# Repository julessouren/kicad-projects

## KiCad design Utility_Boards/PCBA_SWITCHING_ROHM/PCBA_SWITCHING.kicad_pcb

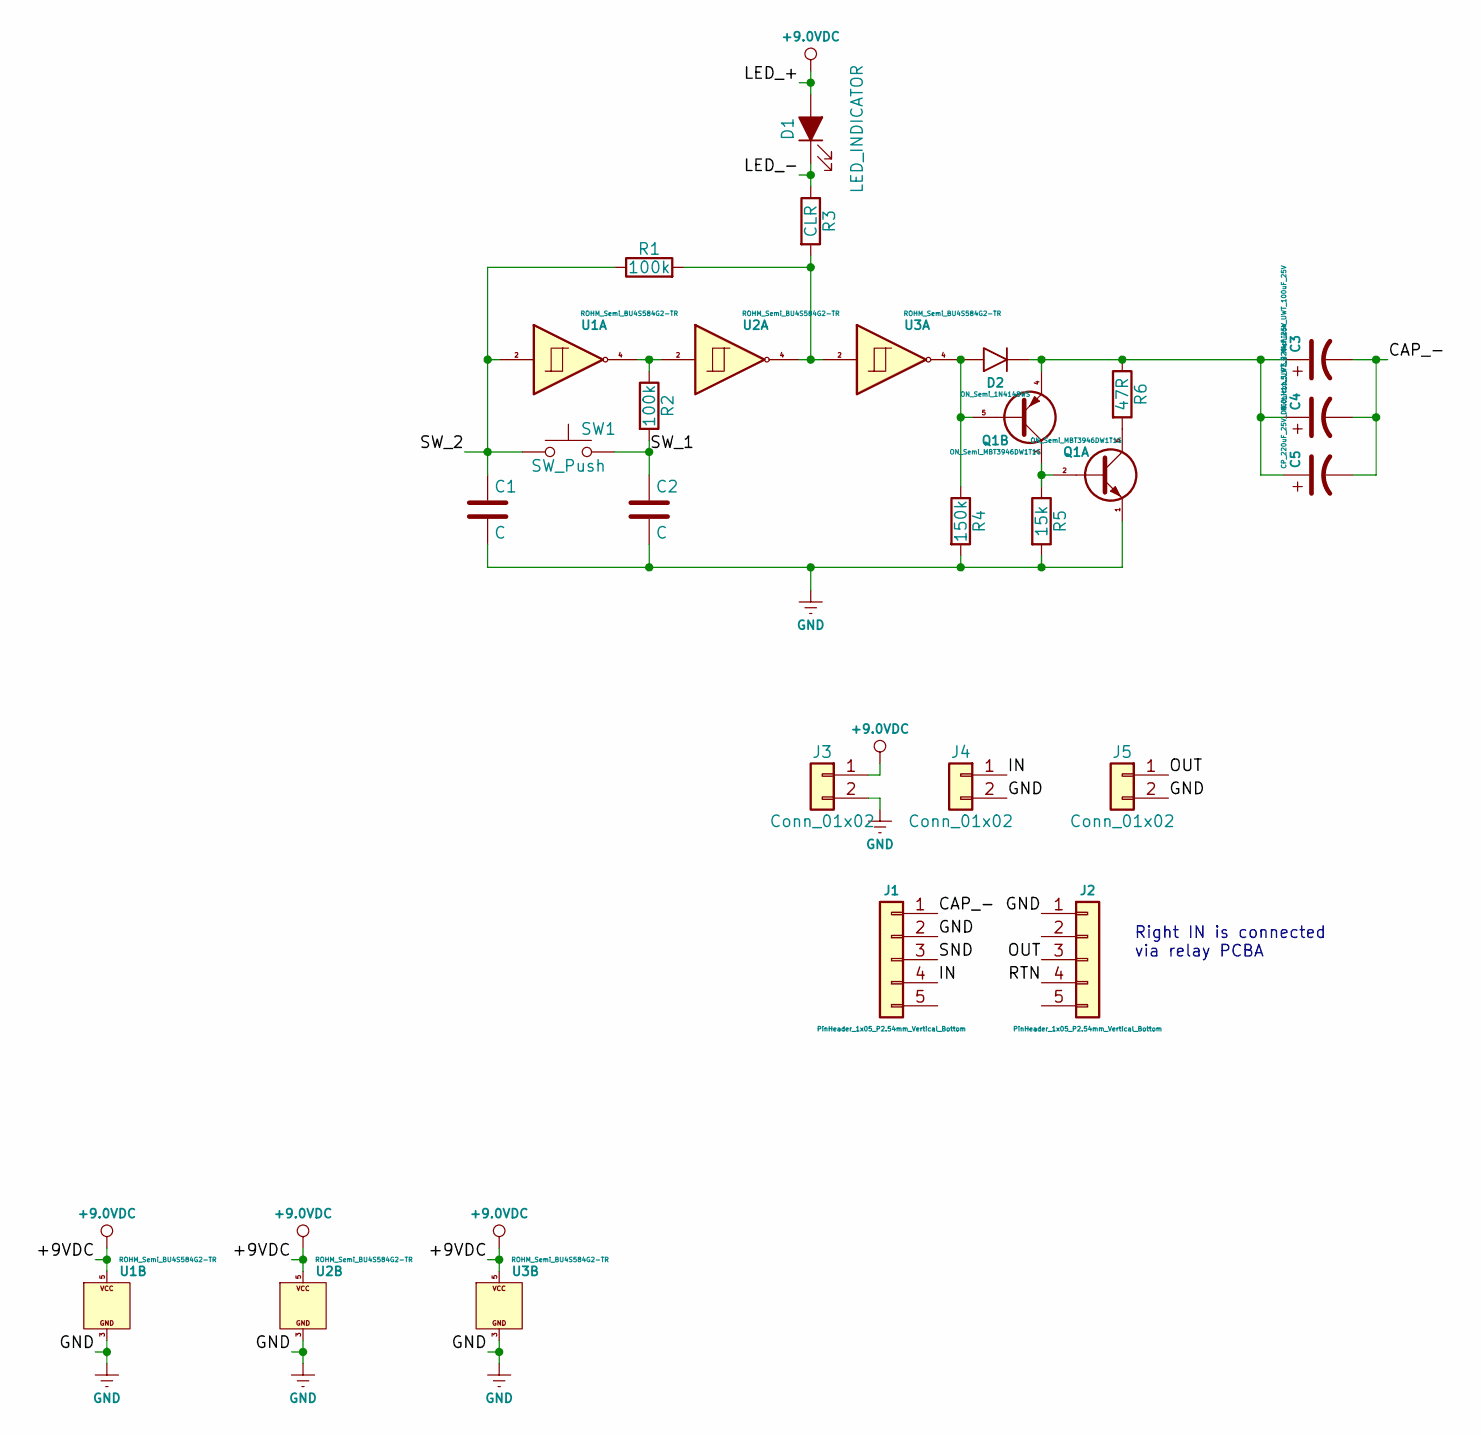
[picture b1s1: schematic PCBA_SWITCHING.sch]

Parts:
C1, C2: C; C_0603_1608M
C3: Nichicon_UWT_100uF_25V; Nichicon_UWT1E101MCL1GS_100uF_25V_6.3x7.7mm
C4: Nichicon_UWT_220uF_25V; Nichicon_UWT1E221MNL1GS_220uF_25V_8.0x10.0mm
C5: CP_220uF_25V_D8.0_H11.5_P3.5; Capacitor_Electrolytic_Radial_D8.0_H11.5_P3.5
D1: LED_INDICATOR; Wire_Pad_2x_1.0mm_Hole_1.5_Annular
D2: ON_Semi_1N4148WS; ON_Semi_1N4148WS_SOD-323F-2
J1, J2: PinHeader_1x05_P2.54mm_Vertical_Bottom; PinHeader_1x05_P2.54mm_Vertical
J3, J4, J5: Conn_01x02; Wire_Pad_2x_1.0mm_Hole_1.5_Annular_2.54mm_Pitch
Q1: ON_Semi_MBT3946DW1T1G; ON_Semi_MBT3946DW1T1G_SOT-363_SC-70-6_SC-80
R1, R2: 100k; R_0603_1608M
R3: CLR; R_0603_1608M
R4: 150k; R_0603_1608M
R5: 15k; R_0603_1608M
R6: 47R; R_0603_1608M
SW1: SW_Push; Wire_Pad_2x_1.0mm_Hole_1.5_Annular_2.54mm_Pitch
U1, U2, U3: ROHM_Semi_BU4S584G2-TR; ROHM_Semi_BU4S584G2-TR_SSOP-5

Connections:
+9.0VDC: D1.2 (A), J3.1, U1.5, U2.5, U3.5
/CAP_-: C3.2, C4.2, C5.2, J1.1
/IN: J1.4, J4.1
/LED_-: D1.1 (K), R3.1
/OUT: J2.3, J5.1
/RTN: J2.4
/SND: J1.3
/SW_1: C2.1, R2.2, SW1.2
/SW_2: C1.1, R1.1, SW1.1, U1.2
GND: C1.2, C2.2, J1.2, J2.1, J3.2, J4.2, J5.2, Q1.1 (E1), R4.2, R5.2, U1.3, U2.3, U3.3
unnamed: C3.1, C4.1, C5.1, D2.1 (K), Q1.4 (E2), R6.1
unnamed: D2.2 (A), Q1.5 (B2), R4.1, U3.4
unnamed: Q1.2 (B1), Q1.3 (C2), R5.1
unnamed: Q1.6 (C1), R6.2
unnamed: R1.2, R3.2, U2.4, U3.2
unnamed: R2.1, U1.4, U2.2

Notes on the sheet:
Right IN is connected via relay PCBA

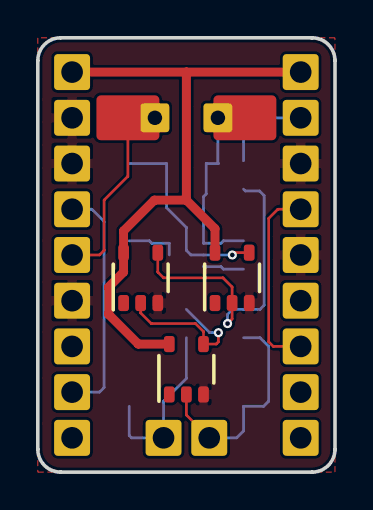
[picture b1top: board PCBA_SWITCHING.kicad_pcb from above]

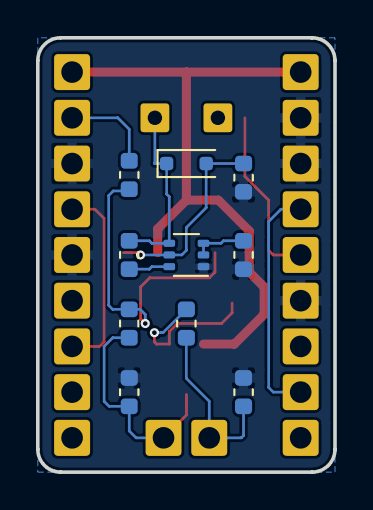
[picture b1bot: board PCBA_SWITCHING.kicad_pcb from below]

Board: 2 copper layers, 16.5 x 24.1 mm, 23 parts (10 on the bottom side), 14 nets.

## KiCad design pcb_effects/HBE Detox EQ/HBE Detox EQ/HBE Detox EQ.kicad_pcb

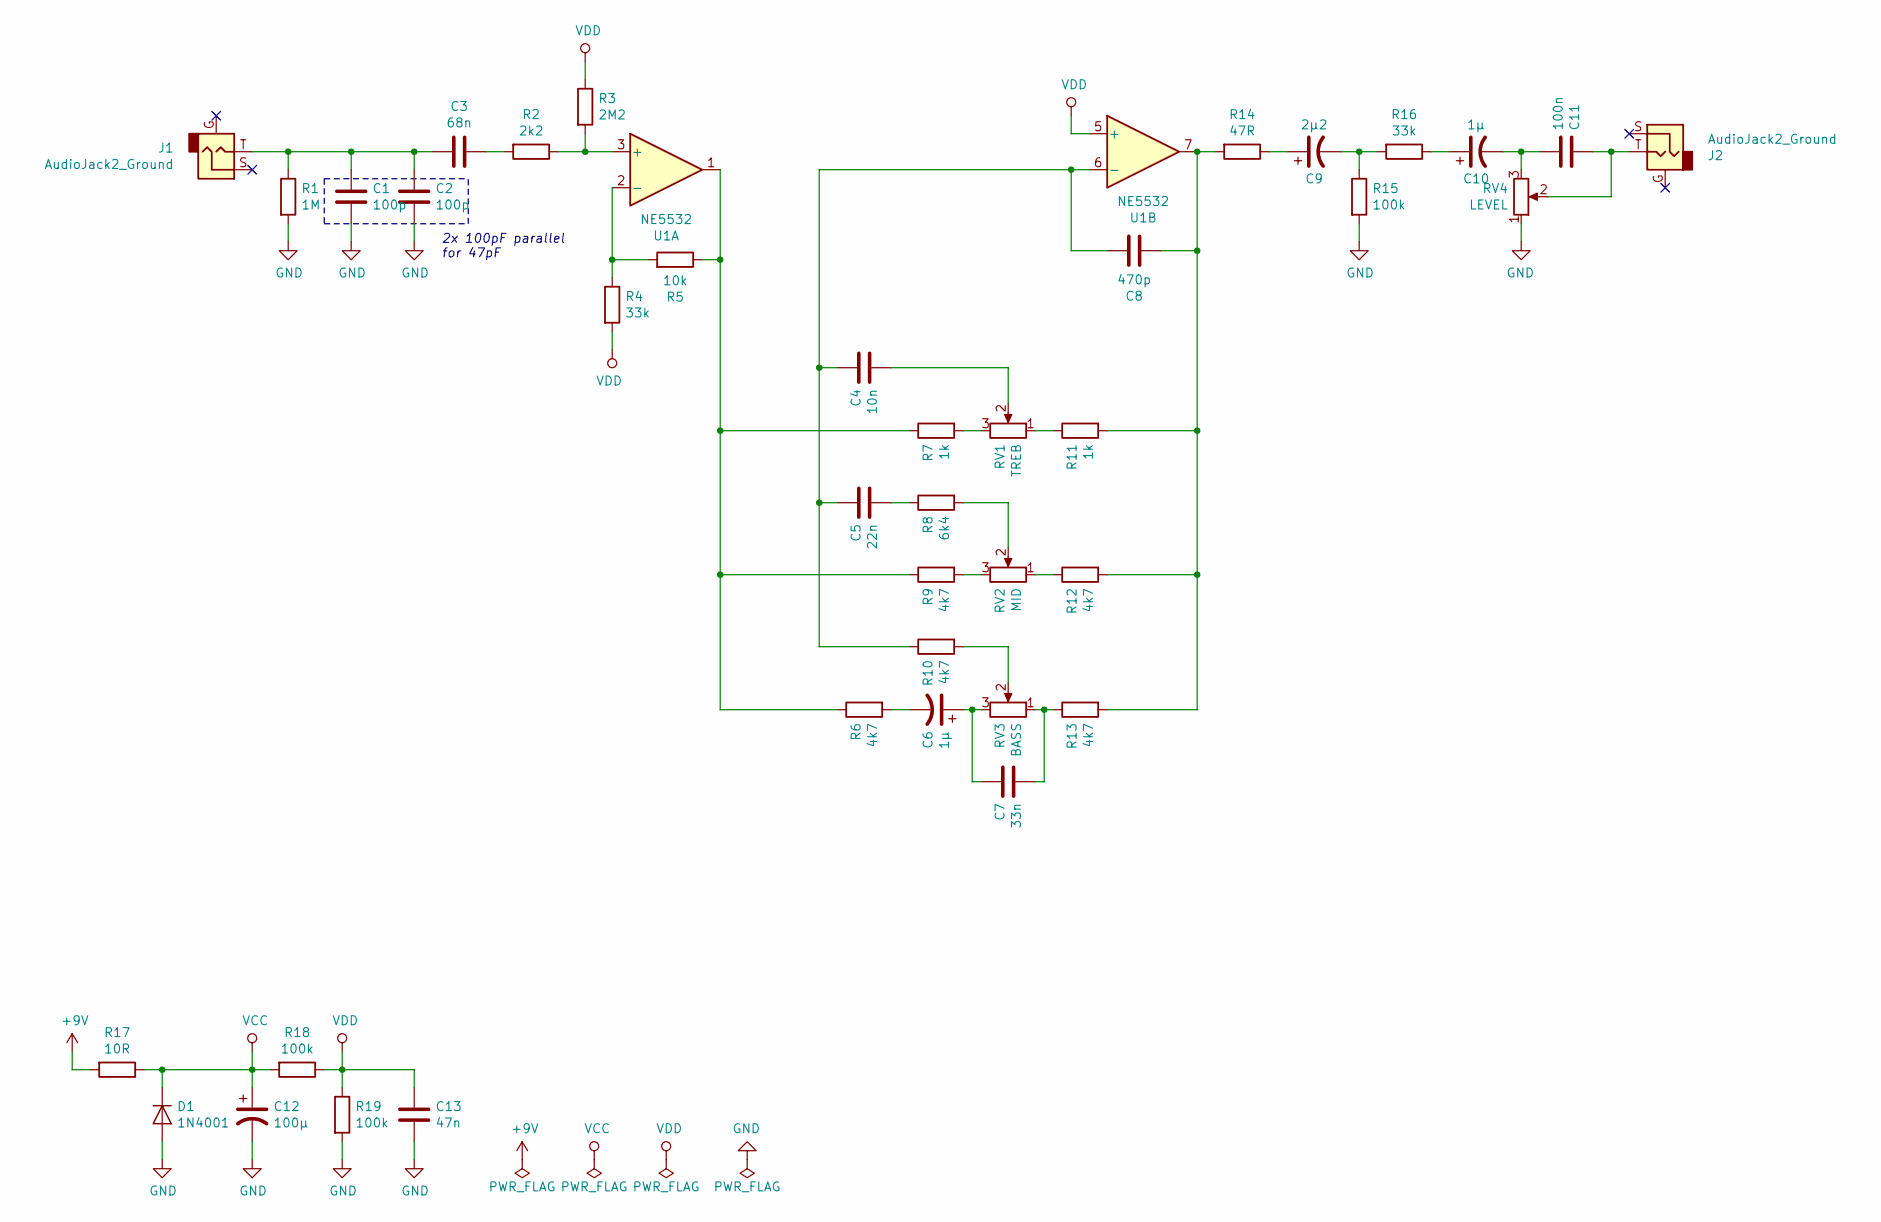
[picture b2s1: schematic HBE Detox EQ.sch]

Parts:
C1, C2: 100p; WIMA_FKP2J001001D00JSSD_100pF_P5.00_7.2x4.5x6.0mm
C3: 68n; WIMA_MKS2F026801C00KSSD_68nF_P5.00_7.2x3.5x8.5mm
C4: 10n; WIMA_FKS2G021001C00KSSD_10nF_P5.00_7.2x3.5x8.5mm
C5: 22n; WIMA_MKS2F022201A00KSSD_22nF_P5.00_7.2x2.5x6.5mm
C6, C10: 1µ; WIMA_MKS2C041001F00KSSD_1.0uF_P5.00_7.2x5.0x10.0mm
C7: 33n; WIMA_MKS2F023301C00KSSD_33nF_P5.00_7.2x3.5x8.5mm
C8: 470p; WIMA_FKP2J004701D00JSSD_470pF_P5.00_7.2x4.5x6.0mm
C9: 2µ2; WIMA_MKS2C042201K00KSSD_2.2uF_P5.00_7.2x7.2x13.0mm
C11: 100n; WIMA_MKS2F031001E00KSSD_100nF_P5.00_7.2x4.5x9.5
C12: 100µ; Nichicon_UWT1E101MCL1GB_100uF_6.3x7.7
C13: 47n; WIMA_MKS2F024701C00KSSD_47nF_P5.00_7.2x3.5x8.5mm
D1: 1N4001; D_SMA
J1, J2: AudioJack2_Ground
R1: 1M; R_0603_1608Metric
R2: 2k2; R_0603_1608Metric
R3: 2M2; R_0603_1608Metric
R4, R16: 33k; R_0603_1608Metric
R5: 10k; R_0603_1608Metric
R6, R9, R10, R12, R13: 4k7; R_0603_1608Metric
R7, R11: 1k; R_0603_1608Metric
R8: 6k4; R_0603_1608Metric
R14: 47R; R_0603_1608Metric
R15, R18, R19: 100k; R_0603_1608Metric
R17: 10R; R_0603_1608Metric
RV1: TREB; Potentiometer_Vishay_148-149_Single_Horizontal
RV2: MID; Potentiometer_Vishay_148-149_Single_Horizontal
RV3: BASS; Potentiometer_Vishay_148-149_Single_Horizontal
RV4: LEVEL; Potentiometer_Vishay_148-149_Single_Horizontal
U1: NE5532; DIP-8_W7.62mm_Socket_LongPads

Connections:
+9V: R17.2
GND: C1.2, C2.2, C12.2, C13.2, D1.2 (A), R1.2, R15.2, R19.2, RV4.1
unnamed: C1.1, C2.1, C3.2, J1.T, R1.1
unnamed: C3.1, R2.2
unnamed: C4.1, C5.1, C8.2, R10.1, U1.6 (-)
unnamed: C4.2, RV1.2
unnamed: C5.2, R8.1
unnamed: C6.1, C7.1, RV3.3
unnamed: C6.2, R6.2
unnamed: C7.2, R13.1, RV3.1
unnamed: C8.1, R11.2, R12.2, R13.2, R14.2, U1.7
unnamed: C9.1, R14.1
unnamed: C9.2, R15.1, R16.2
unnamed: C10.1, R16.1
unnamed: C10.2, C11.2, RV4.3
unnamed: C11.1, J2.T, RV4.2
unnamed: R2.1, R3.2, U1.3 (+)
unnamed: R4.1, R5.2, U1.2 (-)
unnamed: R5.1, R6.1, R7.1, R9.1, U1.1
unnamed: R7.2, RV1.3
unnamed: R8.2, RV2.2
unnamed: R9.2, RV2.3
unnamed: R10.2, RV3.2
unnamed: R11.1, RV1.1
unnamed: R12.1, RV2.1
VCC: C12.1, D1.1 (K), R17.1, R18.2
VDD: C13.1, R3.1, R4.2, R18.1, R19.1, U1.5 (+)

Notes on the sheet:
2x 100pF parallel for 47pF

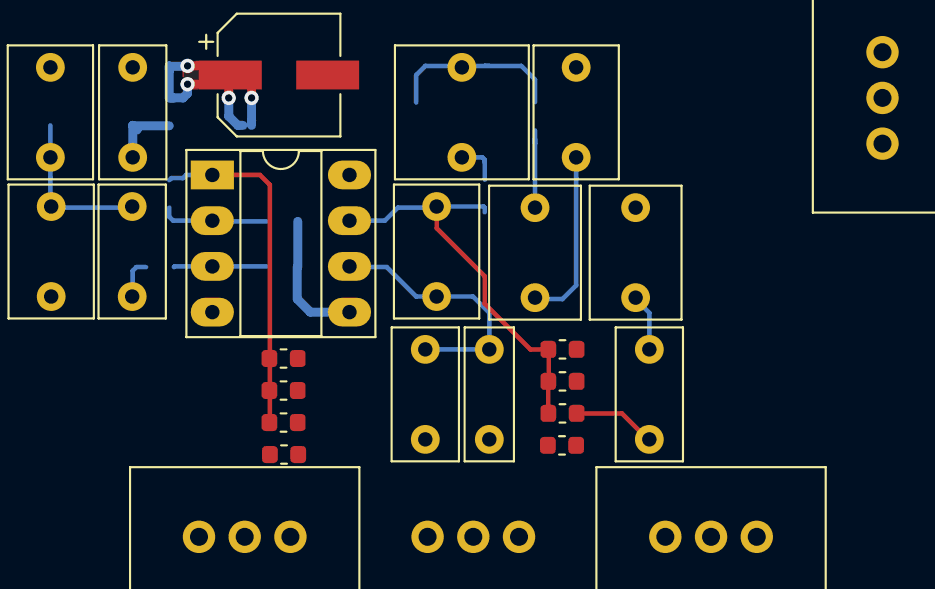
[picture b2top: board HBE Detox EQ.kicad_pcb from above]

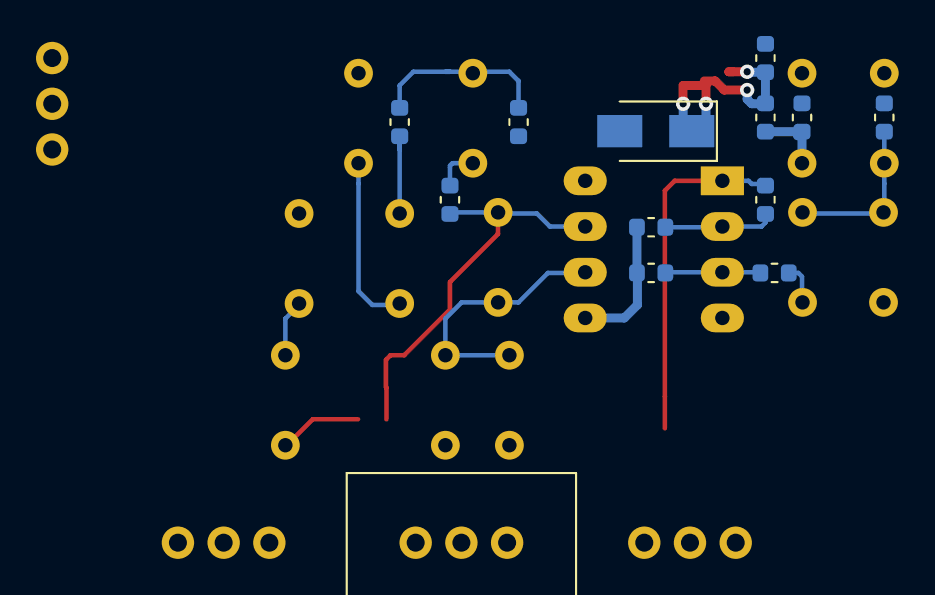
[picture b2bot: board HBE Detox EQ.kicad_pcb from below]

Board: 2 copper layers, 38 parts (13 on the bottom side), 26 nets.

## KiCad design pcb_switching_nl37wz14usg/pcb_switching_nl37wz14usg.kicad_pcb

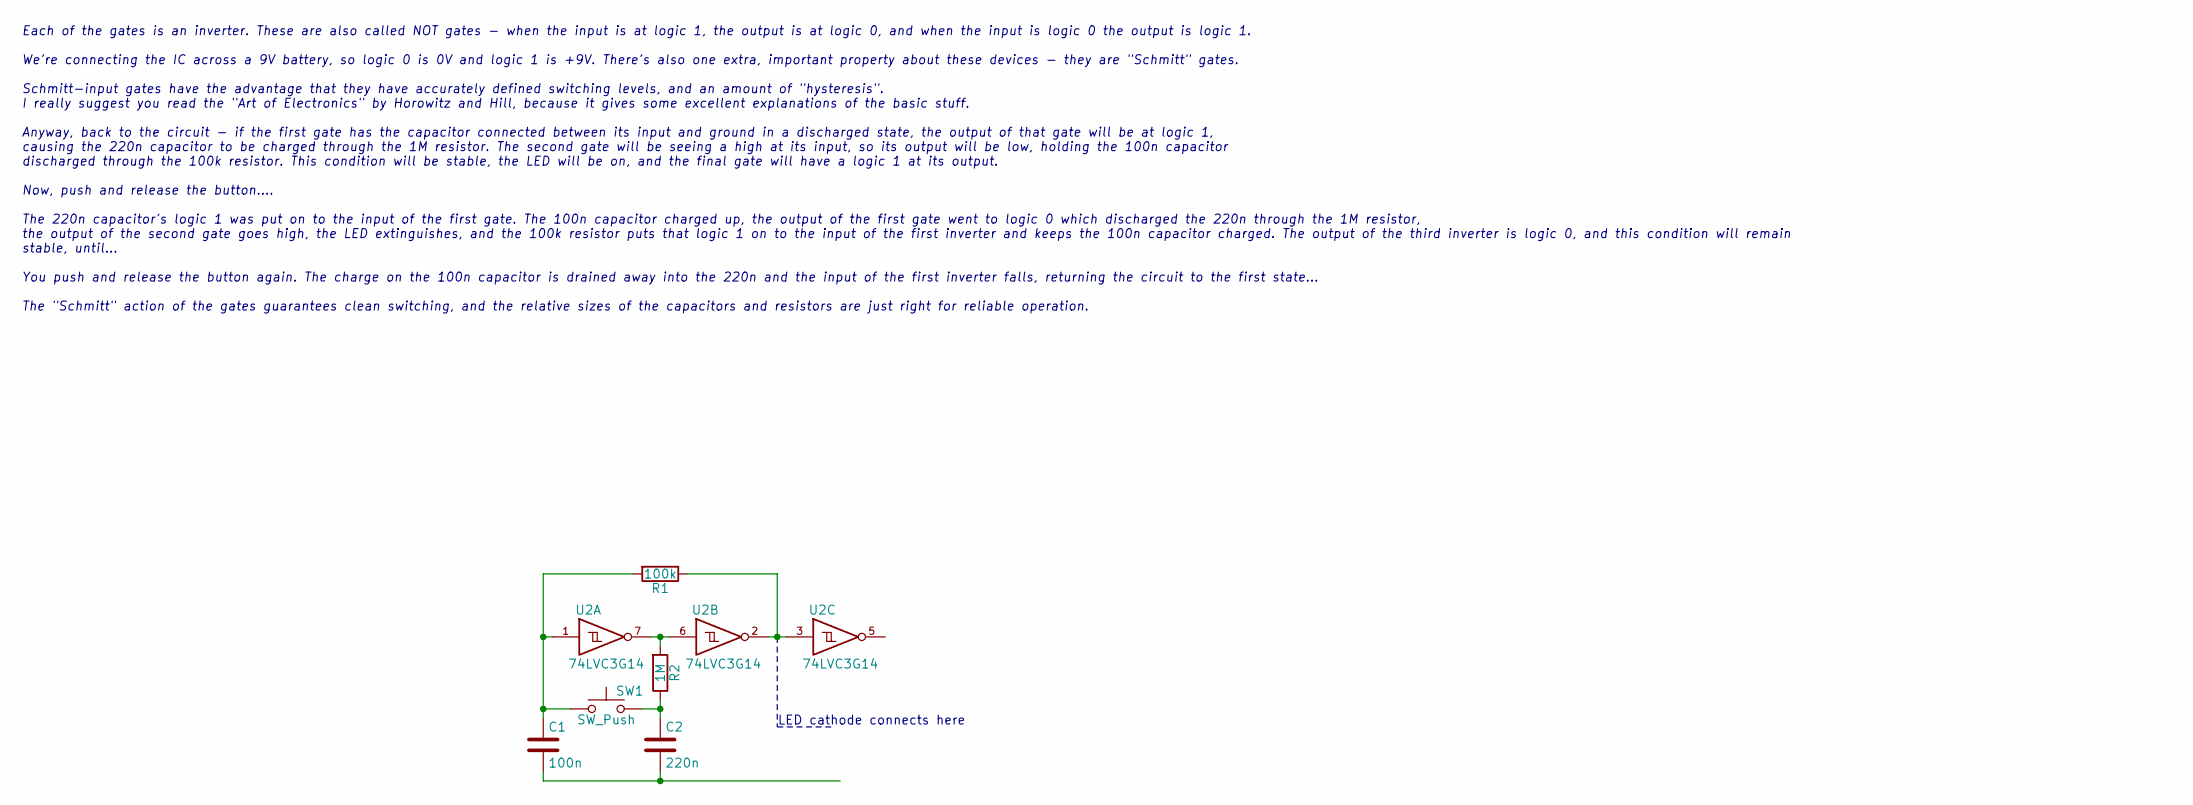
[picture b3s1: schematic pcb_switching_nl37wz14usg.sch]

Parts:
C1: 100n; C_0603_1608Metric
C2: 220n; C_0603_1608Metric
R1: 100k; C_0603_1608Metric
R2: 1M; C_0603_1608Metric
SW1: SW_Push; SolderWirePad_1x02_P3.81mm_Drill1mm
U2: 74LVC3G14; SN74LVC3G14DCTR

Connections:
GND: U2.4 (GND)
unnamed: C1.1, R1.2, SW1.1, U2.1
unnamed: C1.2, C2.2
unnamed: C2.1, R2.1, SW1.2
unnamed: R1.1, U2.2, U2.3
unnamed: R2.2, U2.6, U2.7
VCC: U2.8 (VCC)

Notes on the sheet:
Each of the gates is an inverter. These are also called NOT gates - when the input is at logic 1, the output is at logic 0, and when the input is logic 0 the output is logic 1. We're connecting the IC across a 9V battery, so logic 0 is 0V and logic 1 is +9V. There's also one extra, important proper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
LED cathode connects here

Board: 2 copper layers, 6 parts (0 on the bottom side), 5 nets, no tracks yet.

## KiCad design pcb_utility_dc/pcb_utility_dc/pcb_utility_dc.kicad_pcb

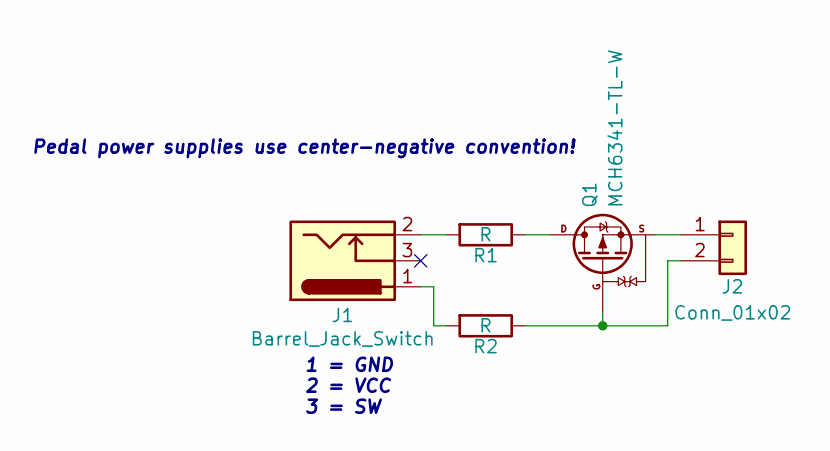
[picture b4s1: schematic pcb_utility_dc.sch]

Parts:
J1: Barrel_Jack_Switch; Jack_DC_Mirrored
J2: Conn_01x02; SolderWirePad_1x02_P3.81mm_Drill0.8mm
Q1: MCH6341-TL-W; ON_Semi_MCH6341-TL-W
R1, R2: R; R_0603_1608Metric

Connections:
unnamed: J1.1, R2.2
unnamed: J1.2, R1.2
unnamed: J2.1, Q1.S
unnamed: J2.2, Q1.G, R2.1
unnamed: Q1.D, R1.1

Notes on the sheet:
Pedal power supplies use center-negative convention!
1 = GND 2 = VCC 3 = SW

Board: 2 copper layers, 5 parts (0 on the bottom side), 5 nets, no tracks yet.
